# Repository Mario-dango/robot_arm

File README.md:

# robot_arm
Proyecto entero sobre el control de un brazo robótico de 4 grados de libertad (4 DOF). Dentro del mismo repositorio estará toda la información y documentación acerca de la construcción del mismo y de los diseños pertinentes para el desarrollo y avances del proyecto.

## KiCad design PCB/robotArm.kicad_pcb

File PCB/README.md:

# ⚡ Diseño Electrónico y PCB - T.A.I.L.S.

Este directorio contiene todo el proyecto de diseño de hardware (Hardware Design) de la placa de control principal para el brazo robótico T.A.I.L.S. 

El diseño fue realizado íntegramente en **KiCad**, buscando crear un placa base robusta que elimine el cableado protoboard, minimice el ruido eléctrico y centralice el control de potencia y señales.

---

## 📐 Diagrama Esquemático

El cerebro de la placa es un microcontrolador **STM32F103C8T6 (Bluepill)**. El circuito está dividido en bloques funcionales para facilitar su análisis y mantenimiento:

### 🧠 Bloques Principales:
1. **Controlador STM32F103C8T6:** Se utiliza cómo nucleo crentral una placa de desarrollo bluepill con el *STM32F103C8T6* cómo microcontrolador principal.

2. **Control de Motores (Ejes X, Y, Z):** Se implementaron 3 zócalos para drivers de motores paso a paso **Pololu A4988**, incluyendo configuración de micro-pasos (MS1, MS2, MS3) y filtrado capacitivo en la alimentación de potencia.

3. **Acondicionamiento de Sensores:** Entradas para 3 finales de carrera (End-Stops). Utiliza transistores PNP (**BC558**) para adaptar y proteger las señales lógicas de 3.3V que van hacia el STM32.

4. **Gestión de Energía:** Etapa de regulación dual. A partir de la tensión de entrada principal (VCC), se extraen **5V** a través de un regulador lineal `LM7805` (para los servos y lógica general) y **3.3V** mediante un regulador ajustable `LM317` (para el STM32 y lógica de sensores).

5. **Interfaz de Usuario y Salidas:** * LEDs indicadores de estado (`HOME`, `WAIT`, `FINISH`).
   * LEDs testigos de tensión (`VCC`, `5V`, `3.3V`).

   * Salida PWM dedicada de 5V para el actuador final (Gripper / Servo).
   * Botón de Parada de Emergencia externo (E-STOP).

---

## 🛤️ Diseño de la Placa (Layout)

*(Aquí puedes colocar una captura del layout 2D de KiCad, mostrando el ruteo de las pistas)*

### Consideraciones de Diseño:
* **Planos de Masa (GND Copper Pours):** Se implementaron polígonos de masa para disipar calor y aislar el ruido de la etapa de conmutación de los motores.
* **Trazas de Potencia:** Dimensionamiento adecuado de pistas para las líneas de VCC y VMOT de los drivers A4988.
* **Motores PaP bipolares:** Conectores SIL para conectar los motores PaP a los drivers de la placa (drivers A4988) siendo:
   -  J1 -> grado X.
   -  J3 -> grado Y.
   -  J4 -> grado Z.

### Indicadores LEDs y salidas de tensión:
* **Alimentaciones:** Posee dos salidas de tensión del regulador lineal, la de la izquierda entrega 5v continuos y de la derecha entrega 3.3v.
* **Indicadores LEDs:** En la placa posee 3 indicadores LEDs que visualizan los estados de Home, Wait y Finish.

### Alimentación:
* **Entradas de la fuente:** Tiene una bornera señalizada donde ingresan los 12v para la alimentación de los motores (Vmot).
* **Reguladores Lineales:**  El mismo bus de tensión Vmot (12v de alimentación) se usa para bajar su tensión a 5v y 3.3v (usando los LM7805 y LM317 respectivamente). Una mejora significativa que se le puede hacer al proyecto es introducir unos step down para ganar en cuanto a eficiencia energetica

### Microcontrolador (STM32F103C8T6):
* **Microcontrolador:** Posee cómo núcleo de procesamiento de las señales y de la comunicación por USB.
* **Pulsadores:** Los botones que poseen en la placa son para parada de emergencia con posibilidad a salida por el conector SIL (J18), además se tiene el botón de reset del algoritmo.

---

## 📦 Modelo 3D

Modelo 3D de la PCB del brazo robótico T.A.I.L.S.

Vista n°1. Superior de la PCB.

Vista n°2.

Vista n°3.

Vista n°4.

Vista n°5. Inferior del LayOut.

Vista n°6. Renderizado superior.

---

## 📋 Lista de Materiales (BOM Principal)
Se puede encontrar dentro de la carpeta [bom](./bom/ibom.html) para completar de forma interactiva y revisar todo acerca de la PCB en cuestión.

---
*Para editar o visualizar el proyecto completo, abre el archivo `.kicad_pro` en KiCad versión 8.0 o superior.*

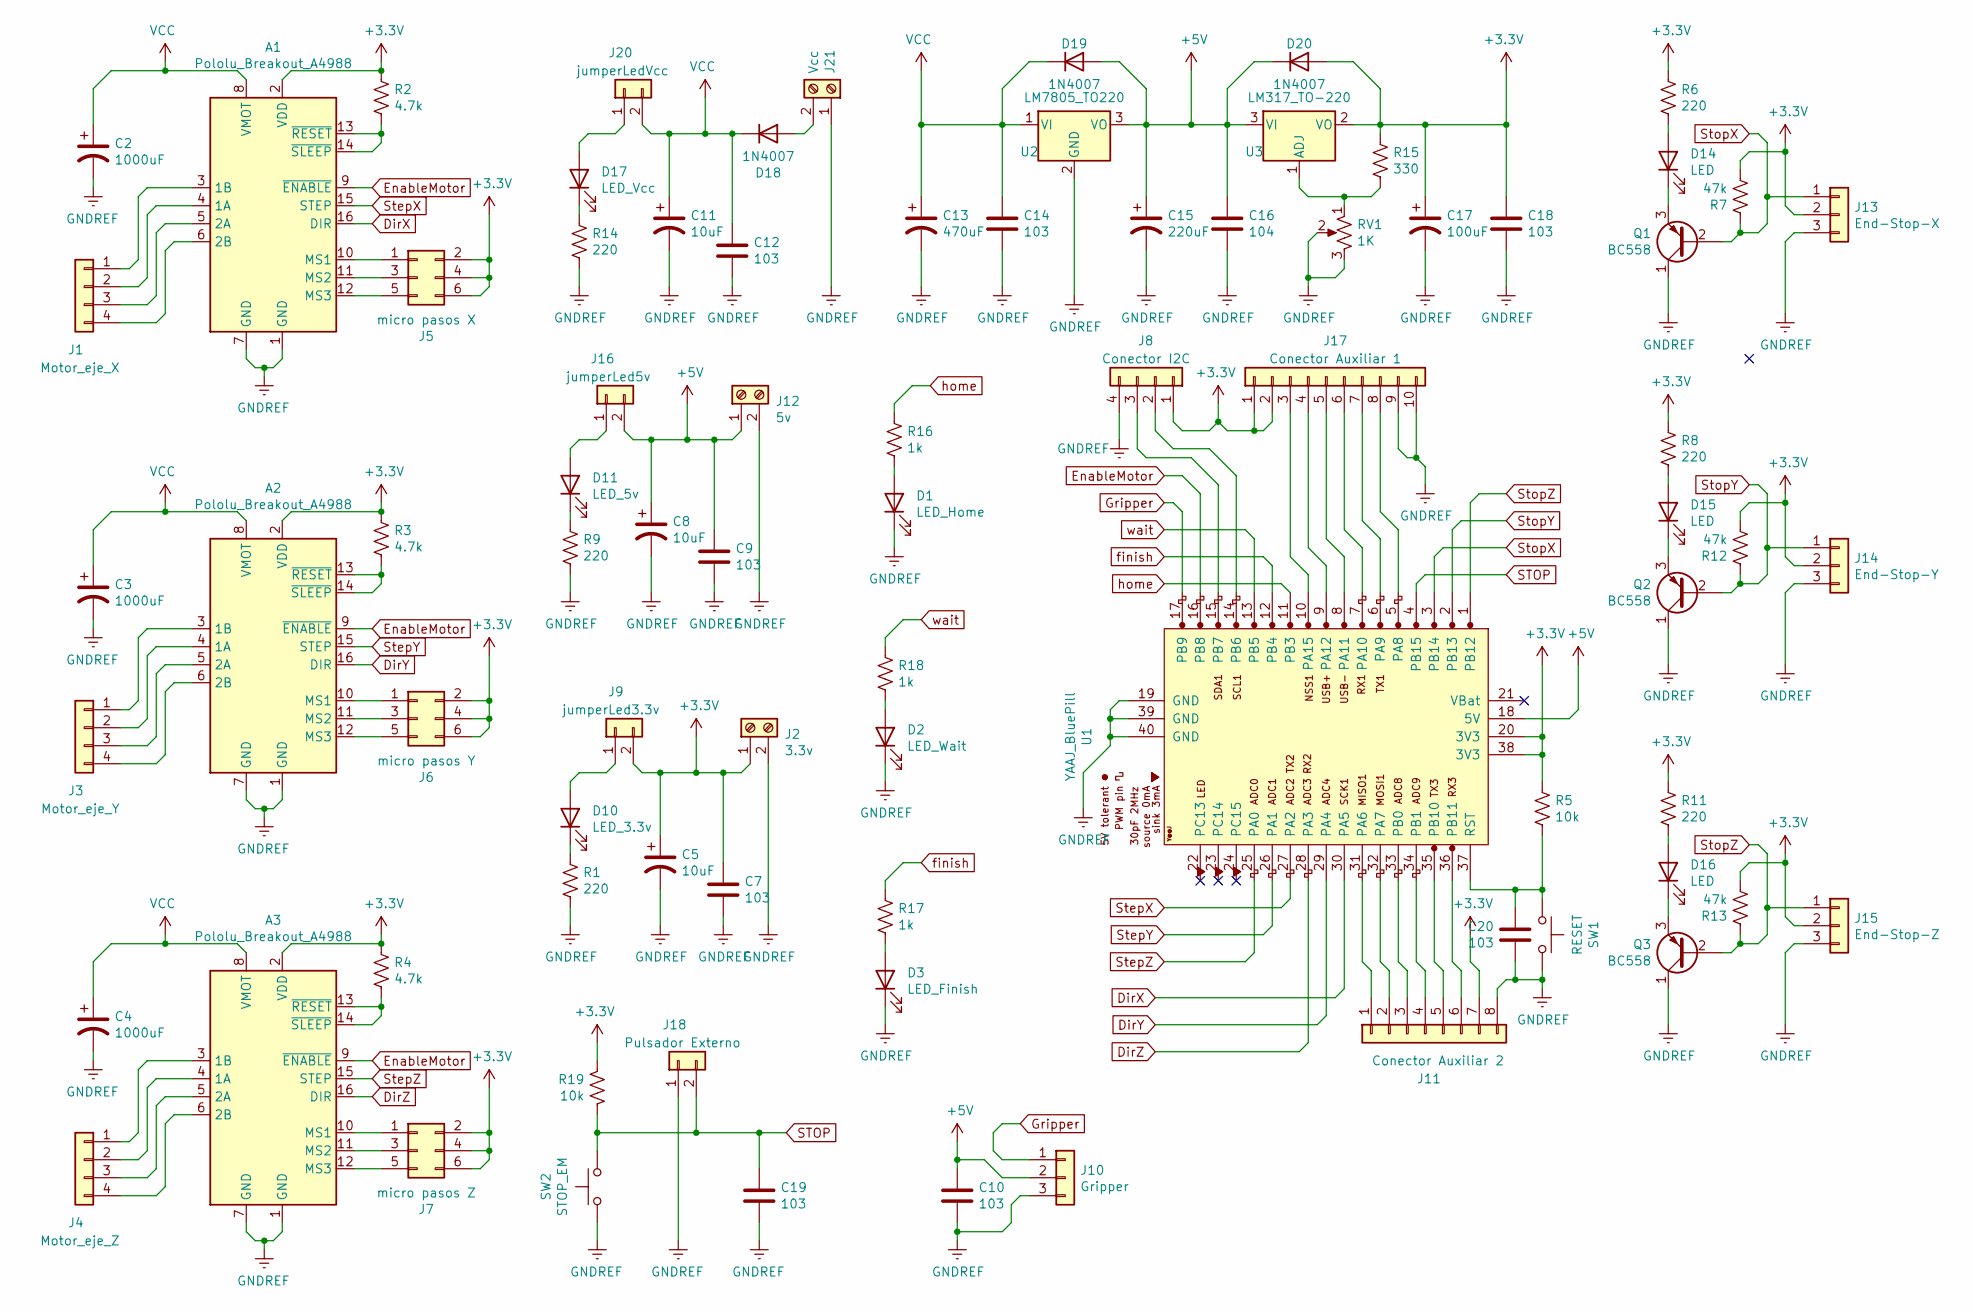
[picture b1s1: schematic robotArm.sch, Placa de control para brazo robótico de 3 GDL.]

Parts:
A1, A2, A3: Pololu_Breakout_A4988; Pololu_Breakout-16_15.2x20.3mm
C2, C3, C4: 1000uF; CP_Radial_D8.0mm_P3.80mm
C5, C8, C11: 10uF; CP_Radial_D8.0mm_P3.80mm
C7, C9, C10, C12, C14, C18, C19, C20: 103; C_Disc_D8.0mm_W2.5mm_P5.00mm
C13: 470uF; CP_Radial_D8.0mm_P3.80mm
C15: 220uF; CP_Radial_D8.0mm_P3.80mm
C16: 104; C_Disc_D8.0mm_W2.5mm_P5.00mm
C17: 100uF; CP_Radial_D8.0mm_P3.80mm
D1: LED_Home; LED_D5.0mm
D2: LED_Wait; LED_D5.0mm
D3: LED_Finish; LED_D5.0mm
D10: LED_3.3v; LED_D5.0mm
D11: LED_5v; LED_D5.0mm
D14, D15, D16: LED; LED_D5.0mm
D17: LED_Vcc; LED_D5.0mm
D18, D19, D20: 1N4007; D_DO-41_SOD81_P10.16mm_Horizontal
J1: Motor_eje_X; PinHeader_1x04_P2.54mm_Vertical
J2: 3.3v; TerminalBlock_bornier-2_P5.08mm
J3: Motor_eje_Y; PinHeader_1x04_P2.54mm_Vertical
J4: Motor_eje_Z; PinHeader_1x04_P2.54mm_Vertical
J5: micro pasos X; PinHeader_2x03_P2.54mm_Vertical
J6: micro pasos Y; PinHeader_2x03_P2.54mm_Vertical
J7: micro pasos Z; PinHeader_2x03_P2.54mm_Vertical
J8: Conector I2C; PinHeader_1x04_P2.54mm_Vertical
J9: jumperLed3.3v; PinHeader_1x02_P2.54mm_Vertical
J10: Gripper; PinHeader_1x03_P2.54mm_Vertical
J11: Conector Auxiliar 2; PinHeader_1x08_P2.54mm_Vertical
J12: 5v; TerminalBlock_bornier-2_P5.08mm
J13: End-Stop-X; PinHeader_1x03_P2.54mm_Vertical
J14: End-Stop-Y; PinHeader_1x03_P2.54mm_Vertical
J15: End-Stop-Z; PinHeader_1x03_P2.54mm_Vertical
J16: jumperLed5v; PinHeader_2x01_P2.54mm_Vertical
J17: Conector Auxiliar 1; PinSocket_1x10_P2.54mm_Vertical
J18: Pulsador Externo; PinHeader_1x02_P2.54mm_Vertical
J20: jumperLedVcc; PinHeader_2x01_P2.54mm_Vertical
J21: Vcc; TerminalBlock_bornier-2_P5.08mm
Q1, Q2, Q3: BC558; TO-92_HandSolder
R1, R6, R8, R9, R11, R14: 220; R_Axial_DIN0207_L6.3mm_D2.5mm_P10.16mm_Horizontal
R2, R3, R4: 4.7k; R_Axial_DIN0207_L6.3mm_D2.5mm_P10.16mm_Horizontal
R5, R19: 10k; R_Axial_DIN0207_L6.3mm_D2.5mm_P10.16mm_Horizontal
R7, R12, R13: 47k; R_Axial_DIN0207_L6.3mm_D2.5mm_P10.16mm_Horizontal
R15: 330; R_Axial_DIN0207_L6.3mm_D2.5mm_P10.16mm_Horizontal
R16, R17, R18: 1k; R_Axial_DIN0207_L6.3mm_D2.5mm_P10.16mm_Horizontal
RV1: 1K; Potentiometer_Bourns_3266W_Vertical
SW1: RESET; SW_PUSH_6mm_H5mm
SW2: STOP_EM; SW_PUSH_6mm_H5mm
U1: YAAJ_BluePill; YAAJ_BluePill_1
U2: LM7805_TO220; TO-220-3_Vertical
U3: LM317_TO-220; TO-220-3_Vertical

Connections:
DirX: A1.16 (DIR), U1.30 (PA5)
DirY: A2.16 (DIR), U1.29 (PA4)
DirZ: A3.16 (DIR), U1.28 (PA3)
EnableMotor: A1.9 (~ENABLE), A2.9 (~ENABLE), A3.9 (~ENABLE), U1.16 (PB8)
GNDREF: A1.1 (GND), A1.7 (GND), A2.1 (GND), A2.7 (GND), A3.1 (GND), A3.7 (GND), C2.2, C3.2, C4.2, C5.2, C7.2, C8.2, C9.2, C10.2, C11.2, C12.2, C13.2, C14.2, C15.2, C16.2, C17.2, C18.2, C19.2, C20.2, D1.1 (K), D2.1 (K), D3.1 (K), J2.2, J8.4, J10.3, J11.8, J12.2, J13.3, J14.3, J15.3, J17.9, J17.10, J18.1, J21.1, Q1.1 (C), Q2.1 (C), Q3.1 (C), R1.2, R9.2, R14.2, RV1.2, RV1.3, SW1.2, SW2.2, U1.19 (GND), U1.39 (GND), U1.40 (GND), U2.2 (GND)
Gripper: J10.1, U1.17 (PB9)
unnamed: A1.3 (1B), J1.1
unnamed: A1.4 (1A), J1.2
unnamed: A1.5 (2A), J1.3
unnamed: A1.6 (2B), J1.4
unnamed: A1.10 (MS1), J5.1
unnamed: A1.11 (MS2), J5.3
unnamed: A1.12 (MS3), J5.5
unnamed: A1.13 (~RESET), A1.14 (~SLEEP), R2.2
unnamed: A2.3 (1B), J3.1
unnamed: A2.4 (1A), J3.2
unnamed: A2.5 (2A), J3.3
unnamed: A2.6 (2B), J3.4
unnamed: A2.10 (MS1), J6.1
unnamed: A2.11 (MS2), J6.3
unnamed: A2.12 (MS3), J6.5
unnamed: A2.13 (~RESET), A2.14 (~SLEEP), R3.2
unnamed: A3.3 (1B), J4.1
unnamed: A3.4 (1A), J4.2
unnamed: A3.5 (2A), J4.3
unnamed: A3.6 (2B), J4.4
unnamed: A3.10 (MS1), J7.1
unnamed: A3.11 (MS2), J7.3
unnamed: A3.12 (MS3), J7.5
unnamed: A3.13 (~RESET), A3.14 (~SLEEP), R4.2
unnamed: C20.1, R5.2, SW1.1, U1.37 (RST)
unnamed: D1.2 (A), R16.2
unnamed: D2.2 (A), R18.2
unnamed: D3.2 (A), R17.2
unnamed: D10.1 (K), R1.1
unnamed: D10.2 (A), J9.1
unnamed: D11.1 (K), R9.1
unnamed: D11.2 (A), J16.1
unnamed: D14.1 (K), Q1.3 (E)
unnamed: D14.2 (A), R6.2
unnamed: D15.1 (K), Q2.3 (E)
unnamed: D15.2 (A), R8.2
unnamed: D16.1 (K), Q3.3 (E)
unnamed: D16.2 (A), R11.2
unnamed: D17.1 (K), R14.1
unnamed: D17.2 (A), J20.1
unnamed: D18.2 (A), J21.2
unnamed: J8.2, U1.14 (PB6)
unnamed: J8.3, U1.15 (PB7)
unnamed: J11.1, U1.31 (PA6)
unnamed: J11.2, U1.32 (PA7)
unnamed: J11.3, U1.33 (PB0)
unnamed: J11.4, U1.34 (PB1)
unnamed: J11.5, U1.35 (PB10)
unnamed: J11.6, U1.36 (PB11)
unnamed: J17.3, U1.10 (PA15)
unnamed: J17.4, U1.9 (PA12)
unnamed: J17.5, U1.8 (PA11)
unnamed: J17.6, U1.7 (PA10)
unnamed: J17.7, U1.6 (PA9)
unnamed: J17.8, U1.5 (PA8)
unnamed: R15.2, RV1.1, U3.1 (ADJ)
STOP: C19.1, J18.2, R19.2, SW2.1, U1.4 (PB15)
StepX: A1.15 (STEP), U1.27 (PA2)
StepY: A2.15 (STEP), U1.26 (PA1)
StepZ: A3.15 (STEP), U1.25 (PA0)
StopX: J13.1, Q1.2 (B), R7.1, U1.3 (PB14)
StopY: J14.1, Q2.2 (B), R12.1, U1.2 (PB13)
StopZ: J15.1, Q3.2 (B), R13.1, U1.1 (PB12)
VCC: A1.8 (VMOT), A2.8 (VMOT), A3.8 (VMOT), C2.1, C3.1, C4.1, C11.1, C12.1, C13.1, C14.1, D18.1 (K), D19.1 (K), J20.2, U2.1 (VI)
finish: R17.1, U1.12 (PB4)
home: R16.1, U1.11 (PB3)
wait: R18.1, U1.13 (PB5)

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
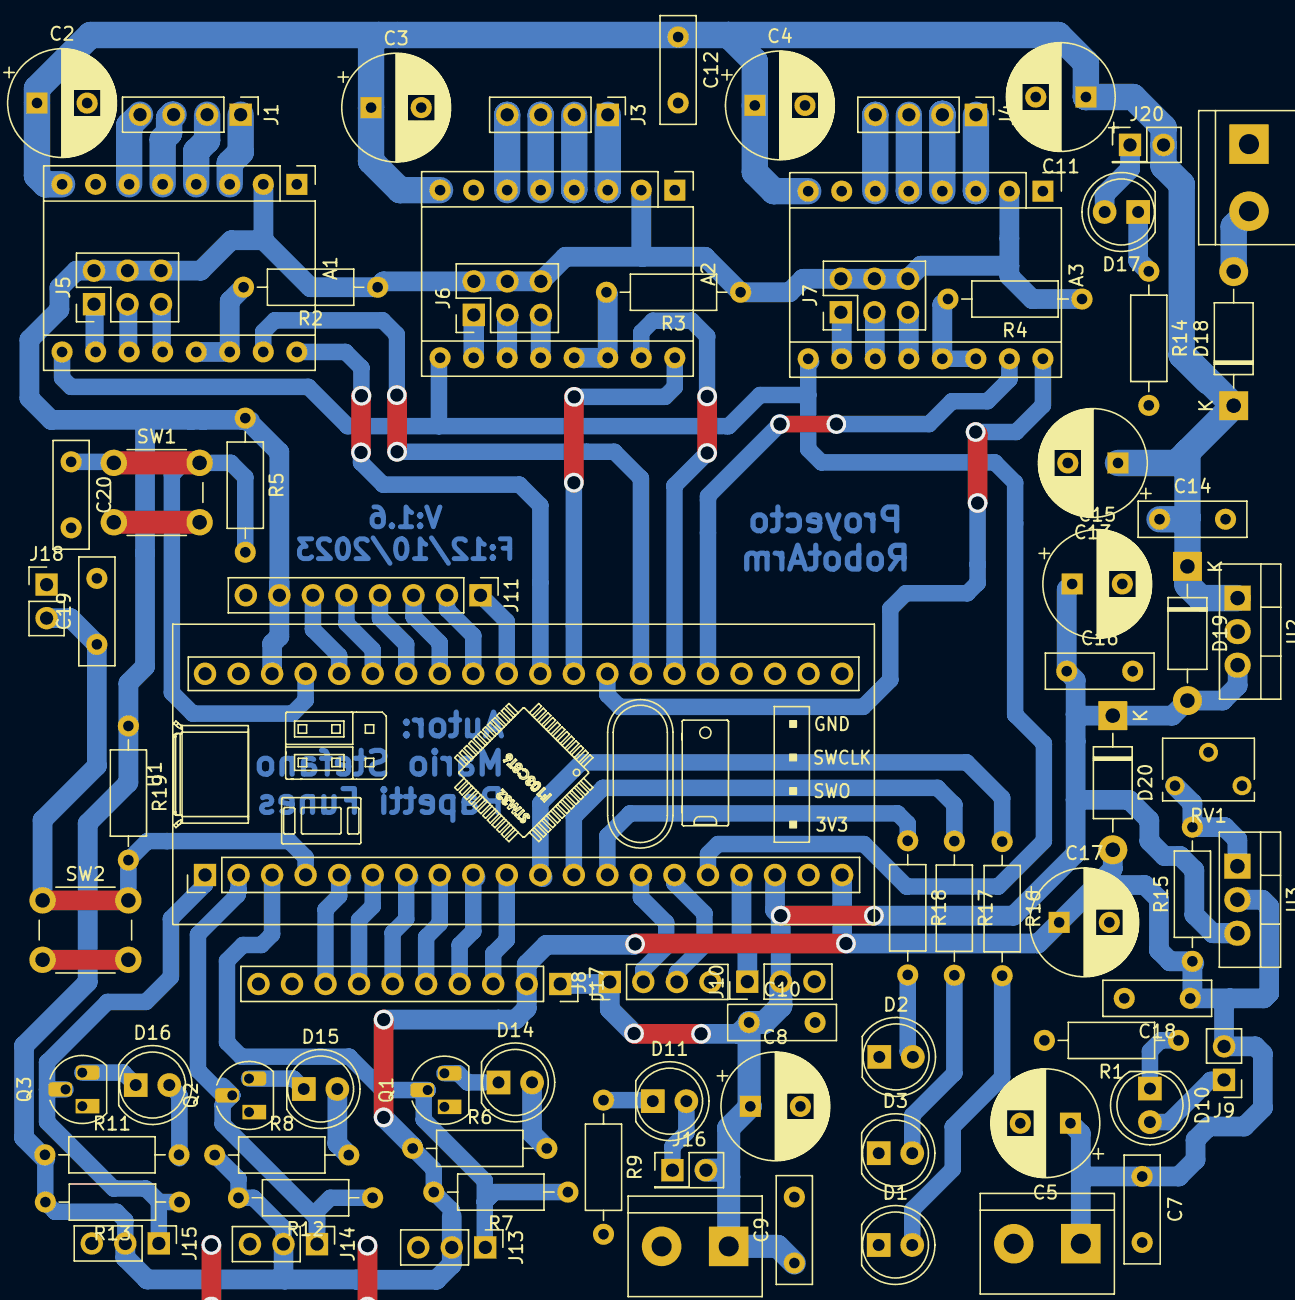
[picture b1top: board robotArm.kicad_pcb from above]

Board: 2 copper layers, 80 parts (0 on the bottom side), 75 nets.

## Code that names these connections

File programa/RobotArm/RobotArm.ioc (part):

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Mcu.Name=STM32F103C(8-B)Tx
Mcu.Package=LQFP48
Mcu.UserName=STM32F103C8Tx
PA0-WKUP.GPIOParameters=GPIO_Label
PA0-WKUP.GPIO_Label=StepM_Z
PA0-WKUP.Signal=GPIO_Output
PA1.GPIOParameters=GPIO_Label
PA1.GPIO_Label=StepM_Y
PA1.Signal=GPIO_Output
PA11.Mode=Device
PA11.Signal=USB_DM
PA12.Mode=Device
PA12.Signal=USB_DP
PA13.Mode=Serial_Wire
PA13.Signal=SYS_JTMS-SWDIO
PA14.Mode=Serial_Wire
PA14.Signal=SYS_JTCK-SWCLK
PA2.GPIOParameters=GPIO_Label
PA2.GPIO_Label=StepM_X
PA2.Signal=GPIO_Output
PA3.GPIOParameters=GPIO_Label
PA3.GPIO_Label=DirM_Z
PA3.Signal=GPIO_Output
PA4.GPIOParameters=GPIO_Label
PA4.GPIO_Label=DirM_Y
PA4.Signal=GPIO_Output
PA5.GPIOParameters=GPIO_Label
PA5.GPIO_Label=DirM_X
PA5.Signal=GPIO_Output
PB12.GPIOParameters=GPIO_Label
PB12.GPIO_Label=StopM_Z
PB12.Signal=GPXTI12
PB13.GPIOParameters=GPIO_Label
PB13.GPIO_Label=StopM_Y
PB13.Signal=GPXTI13
PB14.GPIOParameters=GPIO_Label
PB14.GPIO_Label=StopM_X
PB14.Signal=GPXTI14
PB15.GPIOParameters=GPIO_Label
PB15.GPIO_Label=STOP_btn
PB15.Signal=GPXTI15
PB3.GPIOParameters=GPIO_Label
PB3.GPIO_Label=Home_led
PB3.Signal=GPIO_Output
PB4.GPIOParameters=GPIO_Label
PB4.GPIO_Label=Finish_led
PB4.Signal=GPIO_Output
PB5.GPIOParameters=GPIO_Label
PB5.GPIO_Label=Wait_led
PB5.Signal=GPIO_Output
PB6.Mode=I2C
PB6.Signal=I2C1_SCL
PB7.Mode=I2C
PB7.Signal=I2C1_SDA
PB8.GPIOParameters=GPIO_Label
PB8.GPIO_Label=EnableMotors
PB8.Signal=GPIO_Output
PB9.GPIOParameters=GPIO_Label
PB9.GPIO_Label=Gripper_pin
PB9.Signal=S_TIM4_CH4
PC13-TAMPER-RTC.GPIOParameters=GPIO_Label
PC13-TAMPER-RTC.GPIO_Label=LedPcb
PC13-TAMPER-RTC.Signal=GPIO_Output
PD0-OSC_IN.Mode=HSE-External-Oscillator
PD0-OSC_IN.Signal=RCC_OSC_IN
PD1-OSC_OUT.Mode=HSE-External-Oscillator
PD1-OSC_OUT.Signal=RCC_OSC_OUT
RCC.SYSCLKFreq_VALUE=72000000
RCC.SYSCLKSource=RCC_SYSCLKSOURCE_PLLCLK
board=custom

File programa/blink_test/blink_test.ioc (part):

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Mcu.Name=STM32F103C(8-B)Tx
Mcu.Package=LQFP48
Mcu.UserName=STM32F103C8Tx
PA0-WKUP.GPIOParameters=GPIO_Label
PA0-WKUP.GPIO_Label=StepM1
PA0-WKUP.Signal=S_TIM2_CH1_ETR
PA1.GPIOParameters=GPIO_Label
PA1.GPIO_Label=StepM2
PA1.Signal=S_TIM2_CH2
PA10.Mode=Synchronous
PA10.Signal=USART1_RX
PA11.Mode=Device
PA11.Signal=USB_DM
PA12.Mode=Device
PA12.Signal=USB_DP
PA13.Mode=Serial_Wire
PA13.Signal=SYS_JTMS-SWDIO
PA14.Mode=Serial_Wire
PA14.Signal=SYS_JTCK-SWCLK
PA2.GPIOParameters=GPIO_Label
PA2.GPIO_Label=StepM3
PA2.Signal=S_TIM2_CH3
PA3.GPIOParameters=GPIO_Label
PA3.GPIO_Label=ServoMotor
PA3.Signal=S_TIM2_CH4
PA4.GPIOParameters=GPIO_Label
PA4.GPIO_Label=StopM1
PA4.Signal=GPXTI4
PA5.GPIOParameters=GPIO_Label
PA5.GPIO_Label=StopM2
PA5.Signal=GPXTI5
PA6.GPIOParameters=GPIO_Label
PA6.GPIO_Label=StopM3
PA6.Signal=GPXTI6
PA7.GPIOParameters=GPIO_Label
PA7.GPIO_Label=ADC1_IN7
PA7.Signal=ADCx_IN7
PA8.Mode=Synchronous
PA8.Signal=USART1_CK
PA9.Mode=Synchronous
PA9.Signal=USART1_TX
PB0.Signal=ADCx_IN8
PB1.Signal=S_TIM3_CH4
PB6.Mode=I2C
PB6.Signal=I2C1_SCL
PB7.Mode=I2C
PB7.Signal=I2C1_SDA
PC13-TAMPER-RTC.GPIOParameters=GPIO_Label
PC13-TAMPER-RTC.GPIO_Label=LedPcb
PC13-TAMPER-RTC.Signal=GPIO_Output
PC14-OSC32_IN.Mode=LSE-External-Oscillator
PC14-OSC32_IN.Signal=RCC_OSC32_IN
PC15-OSC32_OUT.Mode=LSE-External-Oscillator
PC15-OSC32_OUT.Signal=RCC_OSC32_OUT
PD0-OSC_IN.Mode=HSE-External-Oscillator
PD0-OSC_IN.Signal=RCC_OSC_IN
PD1-OSC_OUT.Mode=HSE-External-Oscillator
PD1-OSC_OUT.Signal=RCC_OSC_OUT
RCC.SYSCLKFreq_VALUE=72000000
RCC.SYSCLKSource=RCC_SYSCLKSOURCE_PLLCLK
board=custom

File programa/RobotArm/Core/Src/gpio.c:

/* USER CODE BEGIN Header */
/**
  ******************************************************************************
  * @file    gpio.c
  * @brief   This file provides code for the configuration
  *          of all used GPIO pins.
  ******************************************************************************
  * @attention
  *
  * Copyright (c) 2023 STMicroelectronics.
  * All rights reserved.
  *
  * This software is licensed under terms that can be found in the LICENSE file
  * in the root directory of this software component.
  * If no LICENSE file comes with this software, it is provided AS-IS.
  *
  ******************************************************************************
  */
/* USER CODE END Header */

/* Includes ------------------------------------------------------------------*/
#include "gpio.h"

/* USER CODE BEGIN 0 */

/* USER CODE END 0 */

/*----------------------------------------------------------------------------*/
/* Configure GPIO                                                             */
/*----------------------------------------------------------------------------*/
/* USER CODE BEGIN 1 */

/* USER CODE END 1 */

/** Configure pins as
        * Analog
        * Input
        * Output
        * EVENT_OUT
        * EXTI
        * Free pins are configured automatically as Analog (this feature is enabled through
        * the Code Generation settings)
*/
void MX_GPIO_Init(void)
{

  GPIO_InitTypeDef GPIO_InitStruct = {0};

  /* GPIO Ports Clock Enable */
  __HAL_RCC_GPIOC_CLK_ENABLE();
  __HAL_RCC_GPIOD_CLK_ENABLE();
  __HAL_RCC_GPIOA_CLK_ENABLE();
  __HAL_RCC_GPIOB_CLK_ENABLE();

  /*Configure GPIO pin Output Level */
  HAL_GPIO_WritePin(LedPcb_GPIO_Port, LedPcb_Pin, GPIO_PIN_RESET);

  /*Configure GPIO pin Output Level */
  HAL_GPIO_WritePin(GPIOA, StepM_Z_Pin|StepM_Y_Pin|StepM_X_Pin|DirM_Z_Pin
                          |DirM_Y_Pin|DirM_X_Pin, GPIO_PIN_RESET);

  /*Configure GPIO pin Output Level */
  HAL_GPIO_WritePin(GPIOB, Home_led_Pin|Finish_led_Pin|Wait_led_Pin|EnableMotors_Pin, GPIO_PIN_RESET);

  /*Configure GPIO pin : PtPin */
  GPIO_InitStruct.Pin = LedPcb_Pin;
  GPIO_InitStruct.Mode = GPIO_MODE_OUTPUT_PP;
  GPIO_InitStruct.Pull = GPIO_NOPULL;
  GPIO_InitStruct.Speed = GPIO_SPEED_FREQ_LOW;
  HAL_GPIO_Init(LedPcb_GPIO_Port, &GPIO_InitStruct);

  /*Configure GPIO pins : PC14 PC15 */
  GPIO_InitStruct.Pin = GPIO_PIN_14|GPIO_PIN_15;
  GPIO_InitStruct.Mode = GPIO_MODE_ANALOG;
  HAL_GPIO_Init(GPIOC, &GPIO_InitStruct);

  /*Configure GPIO pins : PAPin PAPin PAPin PAPin
                           PAPin PAPin */
  GPIO_InitStruct.Pin = StepM_Z_Pin|StepM_Y_Pin|StepM_X_Pin|DirM_Z_Pin
                          |DirM_Y_Pin|DirM_X_Pin;
  GPIO_InitStruct.Mode = GPIO_MODE_OUTPUT_PP;
  GPIO_InitStruct.Pull = GPIO_NOPULL;
  GPIO_InitStruct.Speed = GPIO_SPEED_FREQ_LOW;
  HAL_GPIO_Init(GPIOA, &GPIO_InitStruct);

  /*Configure GPIO pins : PA6 PA7 PA8 PA9
                           PA10 PA15 */
  GPIO_InitStruct.Pin = GPIO_PIN_6|GPIO_PIN_7|GPIO_PIN_8|GPIO_PIN_9
                          |GPIO_PIN_10|GPIO_PIN_15;
  GPIO_InitStruct.Mode = GPIO_MODE_ANALOG;
  HAL_GPIO_Init(GPIOA, &GPIO_InitStruct);

  /*Configure GPIO pins : PB0 PB1 PB2 PB10
                           PB11 */
  GPIO_InitStruct.Pin = GPIO_PIN_0|GPIO_PIN_1|GPIO_PIN_2|GPIO_PIN_10
                          |GPIO_PIN_11;
  GPIO_InitStruct.Mode = GPIO_MODE_ANALOG;
  HAL_GPIO_Init(GPIOB, &GPIO_InitStruct);

  /*Configure GPIO pins : fines de carrera (X/Y/Z) + botón de PARO DE EMERGENCIA.
    STOP_btn_Pin (PB15) faltaba: sin esto la línea EXTI15 nunca se habilitaba y el
    botón físico jamás disparaba la interrupción => el E-STOP no funcionaba.
    SW2 (STOP_EM) es un push NO con debounce: reposo HIGH (pull-up), pulsado = falling. */
  GPIO_InitStruct.Pin = StopM_X_Pin|StopM_Y_Pin|StopM_Z_Pin|STOP_btn_Pin;
  GPIO_InitStruct.Mode = GPIO_MODE_IT_FALLING;
  GPIO_InitStruct.Pull = GPIO_PULLUP;
  HAL_GPIO_Init(GPIOB, &GPIO_InitStruct);

  /*Configure GPIO pins : PBPin PBPin PBPin PBPin */
  GPIO_InitStruct.Pin = Home_led_Pin|Finish_led_Pin|Wait_led_Pin|EnableMotors_Pin;
  GPIO_InitStruct.Mode = GPIO_MODE_OUTPUT_PP;
  GPIO_InitStruct.Pull = GPIO_NOPULL;
  GPIO_InitStruct.Speed = GPIO_SPEED_FREQ_LOW;
  HAL_GPIO_Init(GPIOB, &GPIO_InitStruct);

}

/* USER CODE BEGIN 2 */

/* USER CODE END 2 */

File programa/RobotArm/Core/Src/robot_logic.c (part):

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        const char* nombre = "?";

        switch (c) {
            case 'H': HAL_GPIO_WritePin(Home_led_GPIO_Port,   Home_led_Pin,   st); nombre = "Home";   break;
            case 'W': HAL_GPIO_WritePin(Wait_led_GPIO_Port,   Wait_led_Pin,   st); nombre = "Wait";   break;
            case 'F': HAL_GPIO_WritePin(Finish_led_GPIO_Port, Finish_led_Pin, st); nombre = "Finish"; break;
            case 'P': HAL_GPIO_WritePin(LedPcb_GPIO_Port,     LedPcb_Pin,     st); nombre = "Placa";  break;
            default:
                USB_Print("TEST: LED invalido (use H/W/F/P)\r\n");
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// Reporta por USB el último evento de interrupción, diferenciando su ORIGEN.
// Se llama desde el bucle principal (NO desde la ISR) para no bloquear dentro de
// una interrupción. Deja el log claro de por dónde entró la parada o el tope:
//   - Botón físico de PARO (EXTI PB15)
//   - Comando :-S por software (E-STOP desde la interfaz)
//   - Fin de carrera X / Y / Z (indicando qué eje tocó su sensor)
void Robot_ReportInterrupts(void) {
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
    switch (src) {
        case IRQ_SRC_ESTOP_BTN:
            USB_Print("IRQ|E-STOP: boton fisico (PB15)\r\n");
            break;
        case IRQ_SRC_ESTOP_SW:
            USB_Print("IRQ|E-STOP: comando :-S (software)\r\n");
            break;
        case IRQ_SRC_LIMIT_X:
            USB_Print("IRQ|Fin de carrera: eje X (PB12)\r\n");
            break;
        case IRQ_SRC_LIMIT_Y:
            USB_Print("IRQ|Fin de carrera: eje Y (PB13)\r\n");
            break;
        case IRQ_SRC_LIMIT_Z:
            USB_Print("IRQ|Fin de carrera: eje Z (PB14)\r\n");
            break;
        default:
            break;
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
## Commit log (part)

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2023-06-19 Se ha agregado al controlador de registros, todo lo pertinente al programa y a la PCB.
2023-06-19 se agregó gitignore al proyecto
2023-06-19 programa prueba EjeX con FDC
2023-06-20 Se actualizó programa EjeX_StopX
2023-06-21 Se avanzó con el diseño de la PCB, falta resolver Vin
2023-06-21 Se avanzó con el diseño de la PCB
2023-06-22 Se logró conectar todos lso dispositivos en la PCB
2023-06-27 Update README.md
    Se agregó descripción, introducción y fuentes.
2023-06-27 Se consiguió una primera versión de Eje-Stop funcional
2023-06-27 Se inició una interfaz en python sencilla para la comunicación con el robot
2023-06-27 Se comenzó con conexión USB
2023-09-04 Se agregó LCD i2c y lógica de CDC
2023-10-11 update interface
2023-11-28 Se actualizaron los cambios
2025-12-21 return 2025
